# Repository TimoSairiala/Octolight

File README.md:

# Octolight
This is a smart night light I have done for my kids.

It has two separate modules
a) under bed unit with RBG leds and motion sensor
b) bedside unit with led strip and push button to increase brightness

Basic functionality is that when ever motion is detected from under the bed (that would be me walking next to the bed)
the RGB leds are turned on with full white color. After motion is not detected, the RBG leds are smoothly dimmed to 
calm blue light that is not too bright for night. When button in bedside unit is pressed, it will turn on led strip in 
bedside unit and maximum white light from RBG leds under the bed.

It is called octolight, because my daughter is a big fan of the tv show and bedside unit has a picture of octonauts.
Octonauts picture is printed on a transparent and the led strip is placed behind this, so it will light up nicely
when the lights are on.

It seems it doesn't help my daughter to get any better sleep, but at least I don't have to stumble across dark room while
walking to her ;)

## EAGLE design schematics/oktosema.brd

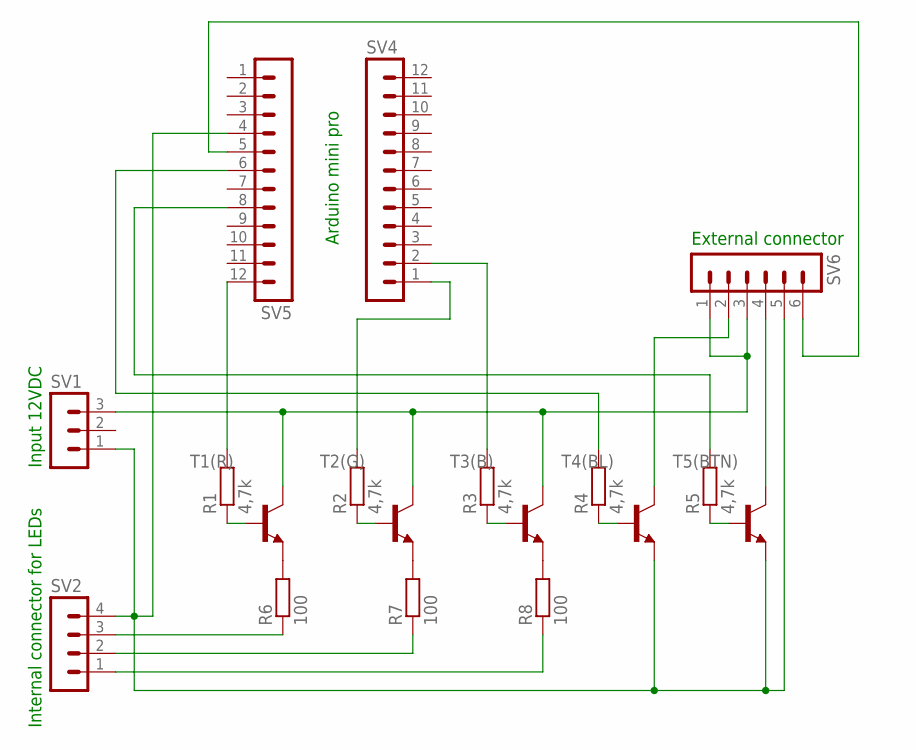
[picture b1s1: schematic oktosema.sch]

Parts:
R1, R2, R3, R4, R5: 4,7k; 0204/7
R6, R7, R8: 100; 0204/7
SV1: MA03-1
SV2: MA04-1
SV4, SV5: MA12-1
SV6: MA06-1
T1(R), T2(G), T3(B), T4(BL), T5(BTN): BC337-25-NPN-TO92-CBE; TO92-CBE

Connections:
unnamed: R1.1, T1(R).B
unnamed: R2.1, T2(G).B
unnamed: R3.1, T3(B).B
unnamed: R4.1, T4(BL).B
unnamed: R5.1, T5(BTN).B
unnamed: R1.2, SV5.12
unnamed: R2.2, SV4.1
unnamed: R3.2, SV4.2
unnamed: R4.2, SV5.6
unnamed: R5.2, SV5.8
unnamed: SV1.3, SV6.1, SV6.3, T1(R).C, T2(G).C, T3(B).C
unnamed: R6.2, T1(R).E
unnamed: R7.2, T2(G).E
unnamed: R8.2, T3(B).E
unnamed: SV6.4, T5(BTN).C
unnamed: R8.1, SV2.1
unnamed: R6.1, SV2.3
unnamed: R7.1, SV2.2
unnamed: SV6.2, T4(BL).C
unnamed: SV5.5, SV6.6
unnamed: SV1.1, SV2.4, SV5.4, SV6.5, T4(BL).E, T5(BTN).E

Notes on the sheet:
Internal connector for LEDs
External connector
Arduino mini pro
Input 12VDC

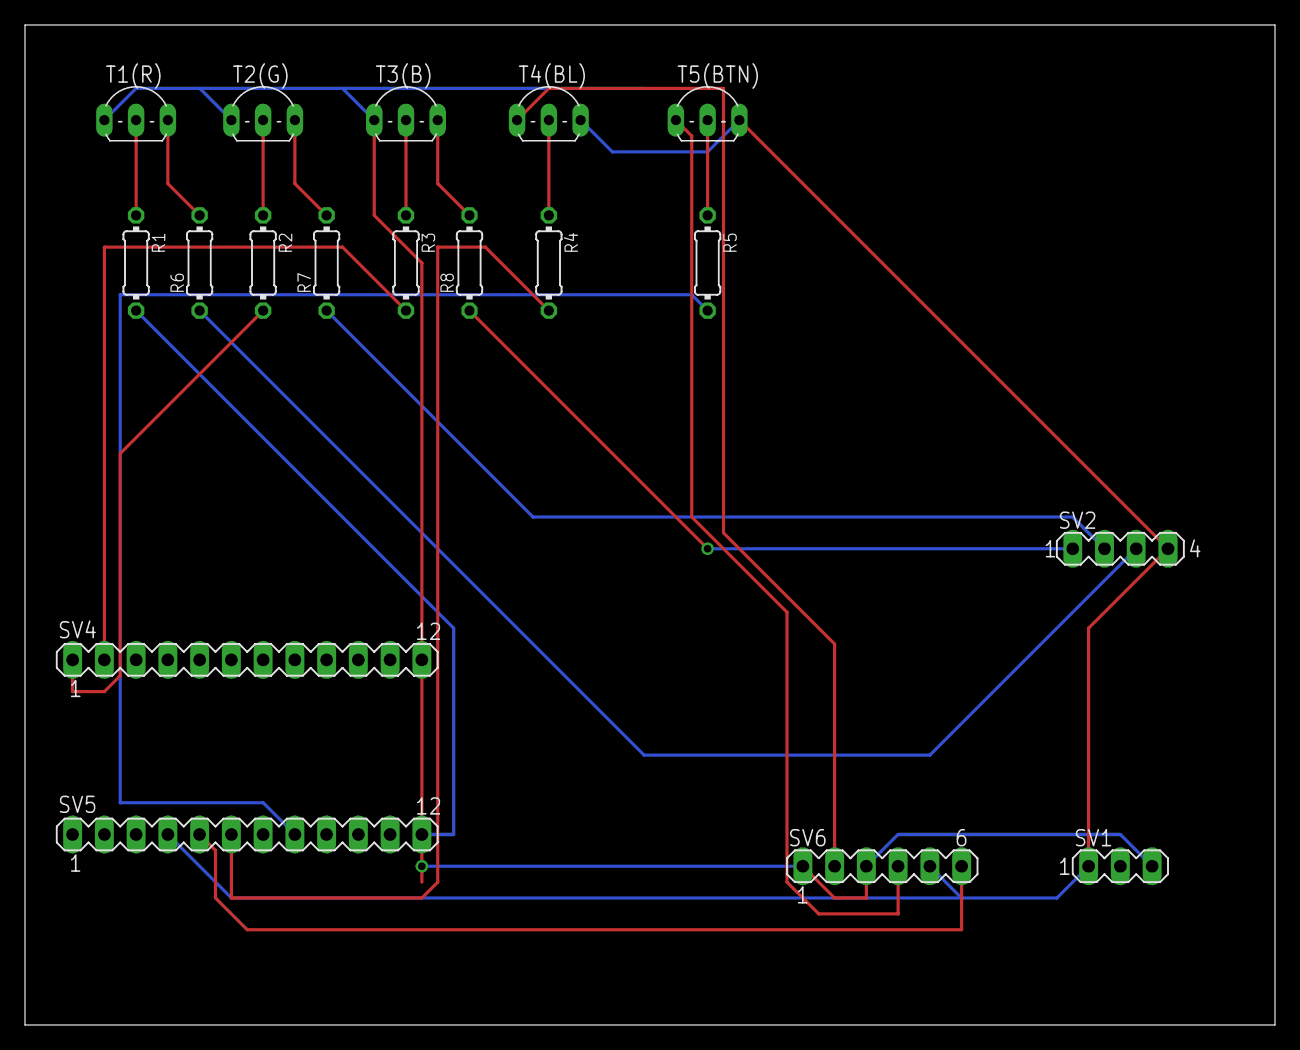
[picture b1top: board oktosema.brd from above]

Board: 2 copper layers, 100.0 x 80.0 mm, 18 parts (0 on the bottom side), 21 nets.

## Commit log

2015-02-13 Initial commit
    Basic octolight functionality.
    It waits for interrupt in pin 2 switching on lights, then dimming those
    gradually.
2015-02-28 Add button backlight
2015-10-06 Removed some white spaces
2015-10-06 Using analogWrite instead of digital
    This enabled pwm output for smooth controlling and fading
    of the lights
2015-10-08 First version of more modular implementation
    Floorlight is separated to its own class. This is to enable
    multiple main lights to work independently of one common
    floorlight
2016-04-06 3D model to print octolight
    This is box with arduino pro mini holder and space for additional
    electronics. It has hole in each wall for rub leds. One wall has
    additional hole for PIR sensor and another wall has holes for power
    cable and wall unit connector.
2016-04-19 Debugging easierify aka light on while power on and some debug prints
2016-04-20 Add schematics draft
2016-04-20 fix delay before dimming
2016-04-21 fixed a spelling mistake
2016-04-25 Add motion detector to pin3 (int1)
2016-04-26 Make arduino holder little bit bigger and increase tolerances
2016-04-26 to help 3D printing, change octonaut logo to another side of the lid
2016-04-26 fix couple of faces inside out
2016-04-28 increase led hole sizes
